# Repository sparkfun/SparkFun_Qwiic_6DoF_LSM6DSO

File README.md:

SparkFun Qwiic 6 Degrees of Freedom Breakout - LSM6DSO
========================================

[*SparkFun Qwiic 6 Degrees of Freedom Breakout - LSM6DSO (SEN-18020)*](https://www.sparkfun.com/products/18020)

The SparkFun LSM6DSO 6 Degrees of Freedom Breakout is an accelerometer and gyroscope sensor with a giant 9kB FIFO buffer and embedded processing interrupt functions. Due to the capabilities and low cost of the LSM6DSO we've created this small breakout board just for you! Each LSM6DSO breakout has been designed to be super-flexible and can be configured specifically for many applications. With the LSM6DSO breakout you will be able to detect shocks, tilt, motion, taps, count steps, and even read the temperature!

The LSM6DSO from STMicroelectronics is capable of reading accelerometer and gyroscope data up to 6.66kHz for more accurate movement sensing. As stated before this breakout also has the ability to buffer up to 9kB of data between reads, host other sensors, and drive interrupt pins all thanks to the LSM6DSO's built-in FIFO.

Utilizing our handy Qwiic system, no soldering is required to connect it to the rest of your system. However, we still have broken out 0.1"-spaced pins in case you prefer to use a breadboard. Each pin has been broken out on the LSM6DSO, with one side of the board featuring power, I<sup>2</sup>C, and SPI functionality while the other side sporting pins that control auxiliary functionality and interrupt outputs. Please keep in mind that the LSM6DSO is a 3.3V device so supplying voltages greater than ~3.6V can permanently damage the IC. A logic level shifter is required for any development platform operating at 5V.

Repository Contents
-------------------

* **/Documentation** - Data sheets, additional product information
* **/Hardware** - Eagle design files (.brd, .sch)
* **/Libraries** - Libraries for use with the LSM6DS3 Breakout
* **/Production** - Production panel files (.brd)

Documentation
--------------

* **[Arduino Library](https://github.com/sparkfun/SparkFun_Qwiic_6DoF_LSM6DSO_Arduino_Library)** - Arduino library for the LSM6DSO Breakout.
* **[Hookup Guide](https://learn.sparkfun.com/tutorials/1664)** - Basic hookup guide for the Qwiic 6DoF LSM6DSO Breakout.
* **[SparkFun Fritzing repo](https://github.com/sparkfun/Fritzing_Parts)** - Fritzing diagrams for SparkFun products.

Product Versions
----------------

* [SEN-18020](https://www.sparkfun.com/products/18020)- Qwiic 6DoF LSM6DSO Breakout

Version History
---------------
* V1.0.0 - Initial product release repository

License Information
-------------------

This product is _**open source**_! 

Please review the LICENSE.md file for license information. 

If you have any questions or concerns on licensing, please contact technical support on our [SparkFun forums](https://forum.sparkfun.com/viewforum.php?f=152).

Distributed as-is; no warranty is given.

- Your friends at SparkFun.

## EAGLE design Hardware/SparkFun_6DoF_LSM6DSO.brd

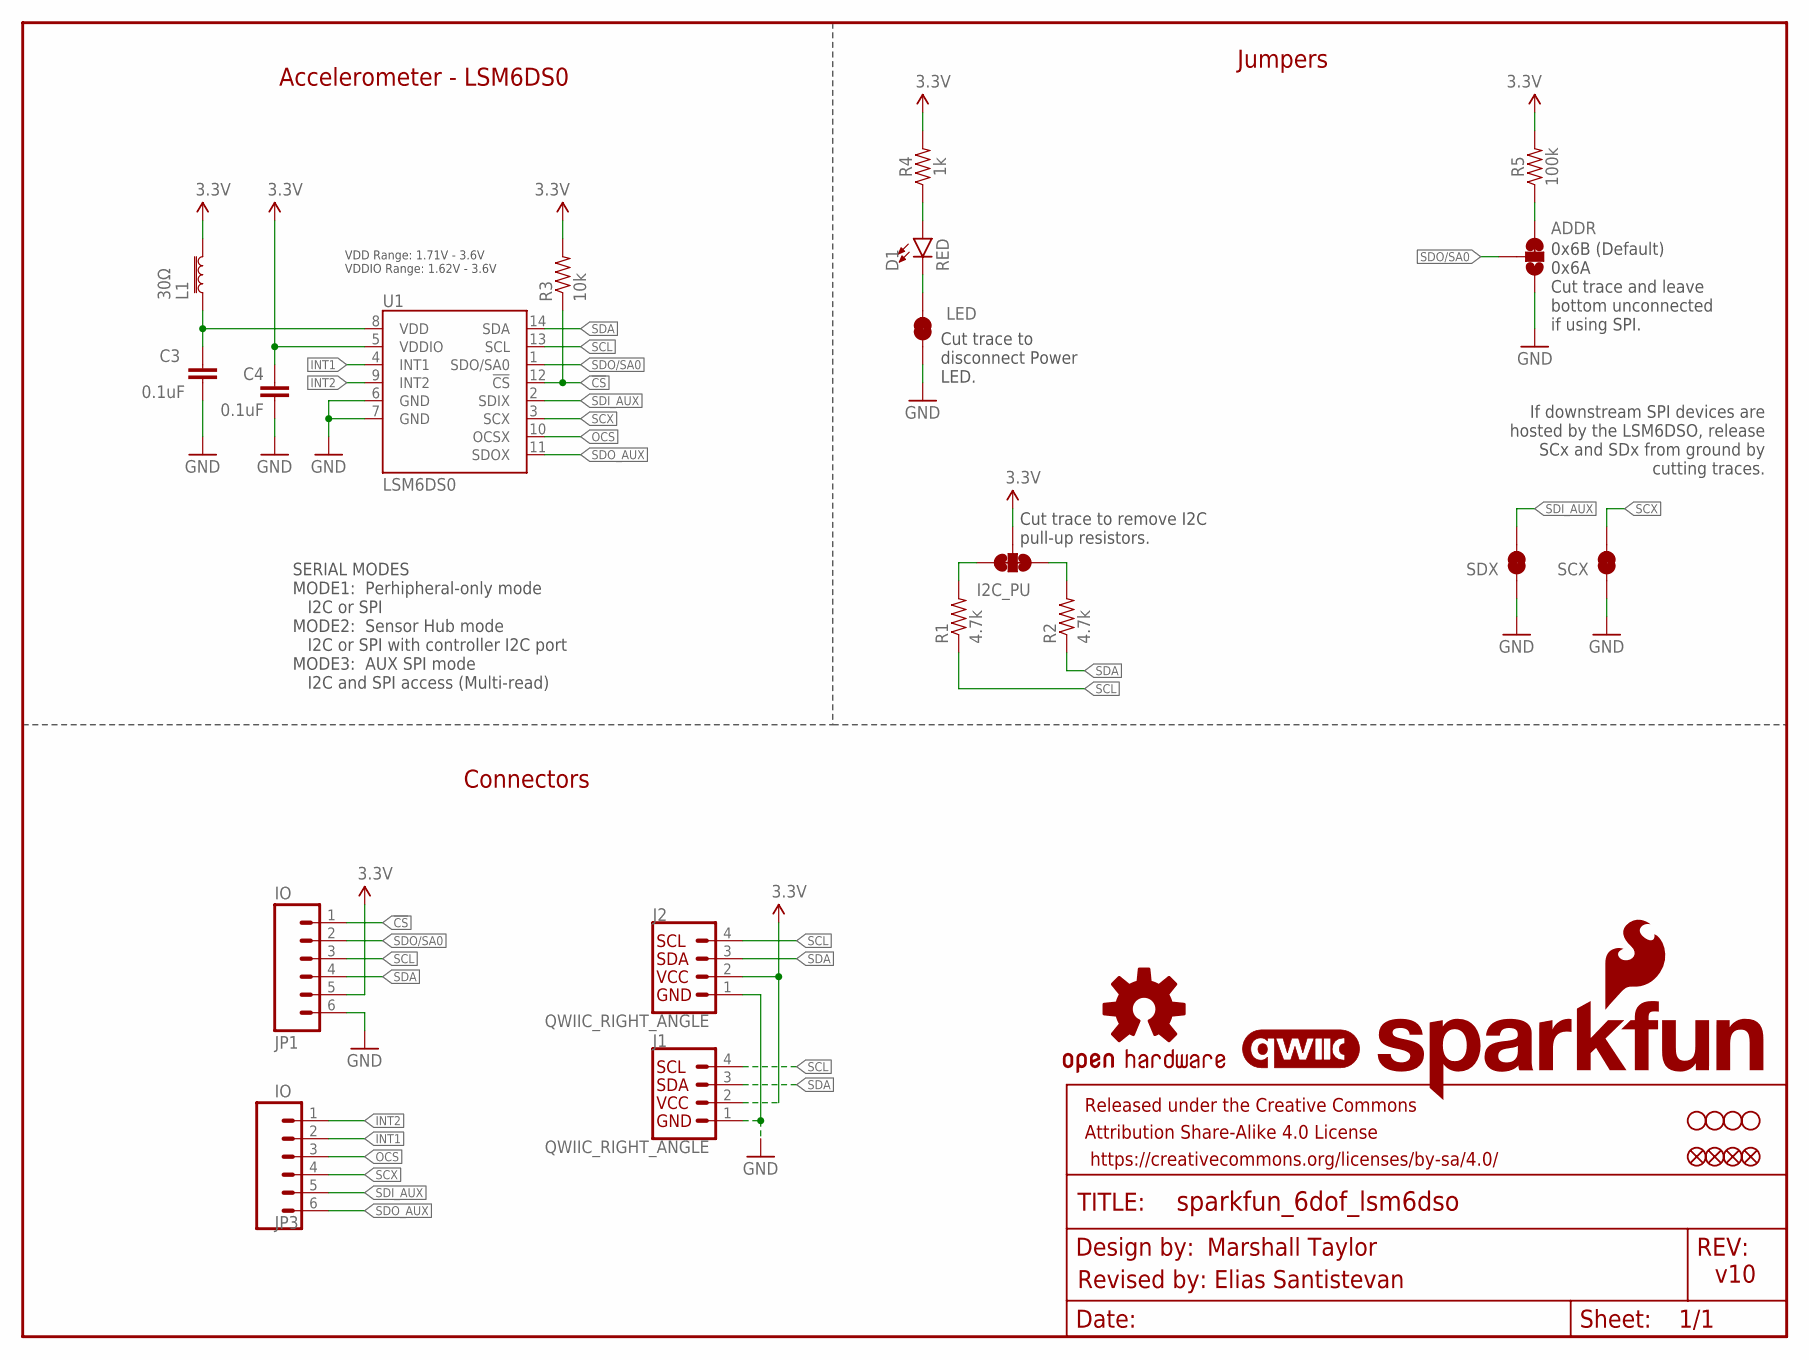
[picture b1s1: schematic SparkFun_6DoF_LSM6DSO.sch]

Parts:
ADDR: JUMPER-SMT_3_1-NC_TRACE_SILK; SMT-JUMPER_3_1-NC_TRACE_SILK
C3, C4: 0.1uF; 0603
D1: RED; LED-0603
FD1, FD2: FIDUCIALUFIDUCIAL; FIDUCIAL-MICRO
FID1, FID2: FIDUCIALUFIDUCIAL; FIDUCIAL-MICRO
FRAME1: FRAME-LETTER; CREATIVE_COMMONS
I2C_PU: S_MODE; SMT-JUMPER_3_2-NC_TRACE_SILK
J1, J2: QWIIC_RIGHT_ANGLE; JST04_1MM_RA
JP1, JP3: IO; 1X06_NO_SILK
L1: 30Ω; 0603
LED: JUMPER-SMT_2_NC_TRACE_SILK; SMT-JUMPER_2_NC_TRACE_SILK
LOGO1: QWIIC_LOGO_4MM; QWIIC_4MM
LOGO2: OSHW-LOGOS; OSHW-LOGO-S
LOGO3: SFE_LOGO_NAME_FLAME.1_INCH; SFE_LOGO_NAME_FLAME_.1
R1, R2: 4.7k; 0603
R3: 10k; 0603
R4: 1k; 0603
R5: 100k; 0603
SCX: JUMPER-SMT_2_NC_TRACE_SILK; SMT-JUMPER_2_NC_TRACE_SILK
SDX: JUMPER-SMT_2_NC_TRACE_SILK; SMT-JUMPER_2_NC_TRACE_SILK
STANDOFF1, STANDOFF2, STANDOFF3, STANDOFF4: STAND-OFFTIGHT; STAND-OFF-TIGHT
U1: LSM6DS0; LGA14L

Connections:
3.3V: C4.1, I2C_PU.2, J1.2, J2.2, JP1.5, L1.1, R3.2, R4.2, R5.2, U1.5 (VDDIO)
!CS!: JP1.1, R3.1, U1.12 (!CS!)
GND: ADDR.1, C3.2, C4.2, J1.1, J2.1, JP1.6, LED.1, SCX.1, SDX.1, U1.6 (GND), U1.7 (GND)
INT1: JP3.2, U1.4 (INT1)
INT2: JP3.1, U1.9 (INT2)
unnamed: ADDR.3, R5.1
unnamed: D1.A, R4.1
unnamed: D1.C, LED.2
unnamed: I2C_PU.1, R1.2
unnamed: I2C_PU.3, R2.2
OCS: JP3.3, U1.10 (OCSX)
SCL: J1.4, J2.4, JP1.3, R1.1, U1.13 (SCL)
SCX: JP3.4, SCX.2, U1.3 (SCX)
SDA: J1.3, J2.3, JP1.4, R2.1, U1.14 (SDA)
SDI_AUX: JP3.5, SDX.2, U1.2 (SDIX)
SDO/SA0: ADDR.2, JP1.2, U1.1 (SDO/SA0)
SDO_AUX: JP3.6, U1.11 (SDOX)
VDD: C3.1, L1.2, U1.8 (VDD)

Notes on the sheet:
Accelerometer - LSM6DS0
If downstream SPI devices are hosted by the LSM6DSO, release SCx and SDx from ground by cutting traces.
Cut trace to remove I2C pull-up resistors.
SERIAL MODES MODE1: Perhipheral-only mode I2C or SPI MODE2: Sensor Hub mode I2C or SPI with controller I2C port MODE3: AUX SPI mode I2C and SPI access (Multi-read)
Revised by: Elias Santistevan
VDD Range: 1.71V - 3.6V VDDIO Range: 1.62V - 3.6V
v10
0x6B (Default) 0x6A Cut trace and leave bottom unconnected if using SPI.
Jumpers
Cut trace to disconnect Power LED.
Connectors

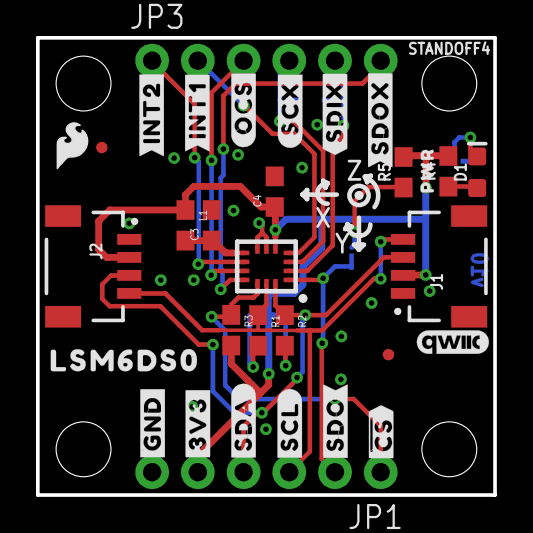
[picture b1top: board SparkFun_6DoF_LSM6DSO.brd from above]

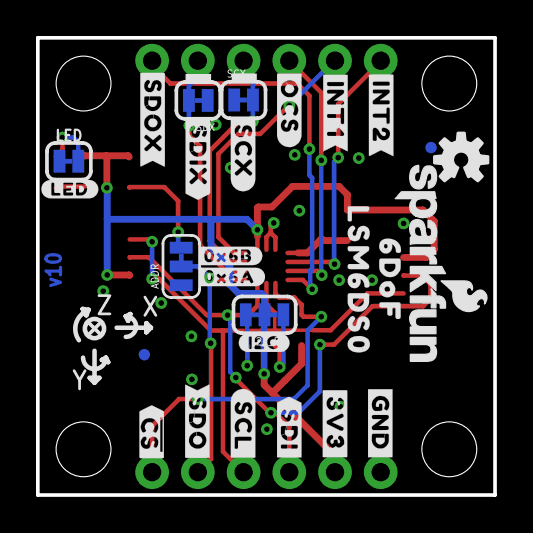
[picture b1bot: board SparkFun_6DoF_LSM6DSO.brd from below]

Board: 2 copper layers, 25.4 x 25.4 mm, 64 parts (27 on the bottom side), 18 nets.

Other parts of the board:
U$1, U$15: #3V3#1
U$2, U$17: #GND#0
U$3: ##CS##7
U$4: #SDA#4
U$5, U$22: #SCL#5
U$6: #SDO#6
U$7, U$19: #INT1#9
U$8, U$21: #INT2#9
U$9: #OCS#8
U$10: #SCX#9
U$11, U$33: #SDIX#11
U$12, U$30: LSM6DS011
U$13: #0X6A#11
U$14: #0X6B#11
U$16: #LED#11
U$18: #SDO#7
U$20: #OCS#7
U$23: #SCX#8
U$24, U$32: #SDOX#12
U$25: #I2C#11
U$26: #SDI#4
U$27: ##CS##8
U$28: PWR8
U$29: SFE_LOGO_FLAME_.1
U$31: 6DOF12

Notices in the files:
parts and their libraries:
SparkFun-Aesthetics: Licensing: Creative Commons ShareAlike 4.0 International - https://creativecommons.org/licenses/by-sa/4.0
SparkFun-Aesthetics: Released under the Creative Commons Attribution Share-Alike 4.0 License
SparkFun-Aesthetics: https://creativecommons.org/licenses/by-sa/4.0
